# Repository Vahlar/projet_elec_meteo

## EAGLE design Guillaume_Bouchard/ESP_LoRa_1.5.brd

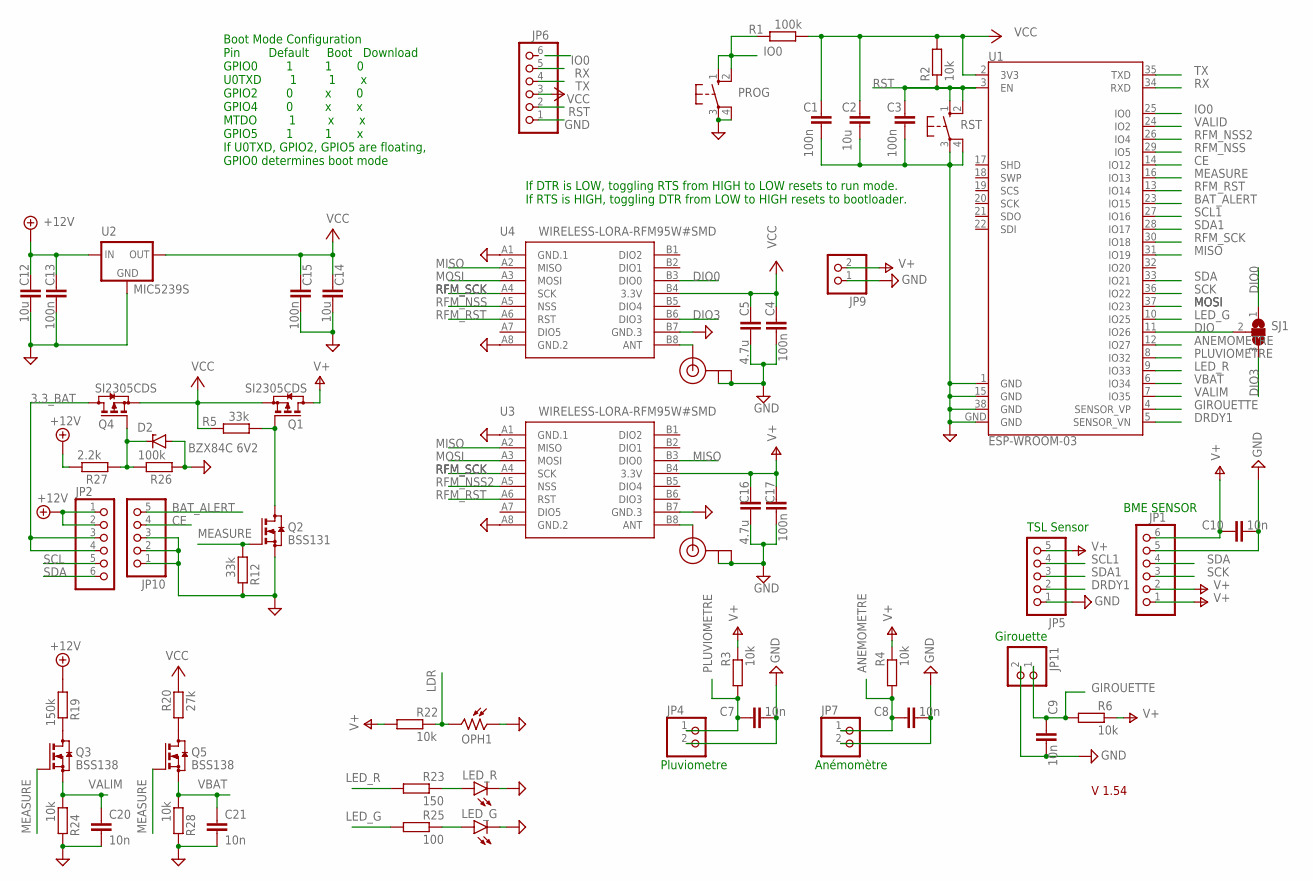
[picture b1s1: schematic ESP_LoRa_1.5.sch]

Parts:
C1, C3, C4, C13, C15, C17: 100n; C1206
C2, C12, C14: 10u; C1210
C5, C16: 4.7u; C1210
C7, C8, C9, C10, C20, C21: 10n; C1206
D2: BZX84C 6V2; TO236
J1, J2: U.FL
JP1, JP2, JP6: PINHD-1X6; 1X06
JP4, JP7, JP9, JP11: PINHD-1X2; 1X02
JP5, JP10: PINHD-1X5; 1X05
LED_G: LEDSMT1206; 1206
LED_R: LEDSMT1206; 1206
OPH1: VT93N2; VT900
PROG: 10-XX; B3F-10XX
Q1, Q4: SI2305CDS; SOT23
Q2: BSS131; SOT23
Q3, Q5: BSS138; SOT23
R1, R26: 100k; R1206
R2, R3, R4, R6, R22, R24, R28: 10k; R1206
R5, R12: 33k; R1206
R19: 150k; R1206
R20: 27k; R1206
R23: 150; R1206
R25: 100; R1206
R27: 2.2k; R1206
RST: 10-XX; B3F-10XX
SJ1: SJ2W; SJ_2
U1: ESP-WROOM-03
U2: MIC5239S; SOT223
U3, U4: WIRELESS-LORA-RFM95W#SMD

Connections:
3.3_BAT: JP2.3, JP2.4, Q4.3 (D)
+12V: C12.1, C13.1, JP2.1, JP2.2, R19.1, R27.2, U2.1 (IN)
ANEMOMETRE: C8.1, JP7.1, R4.1, U1.12 (IO27)
ANT2: J2.3 (SIGNAL), U4.B8 (ANT)
ANT3: J1.3 (SIGNAL), U3.B8 (ANT)
BAT_ALERT: JP10.5, U1.23 (IO15)
CE: JP10.4, U1.14 (IO12)
DIO: SJ1.2, U1.11 (IO26)
DIO0: SJ1.1, U4.B3 (DIO0)
DIO3: SJ1.3, U4.B6 (DIO3)
DRDY1: JP5.2, U1.5 (SENSOR_VN)
GIROUETTE: C9.1, JP11.1, R6.1, U1.4 (SENSOR_VP)
GND: C1.2, C2.2, C3.2, C4.2, C5.2, C7.2, C8.2, C9.2, C10.2, C12.2, C13.2, C14.2, C15.2, C16.2, C17.2, C20.2, C21.2, D2.A, J1.1 (GND), J1.2 (GND), J2.1 (GND), J2.2 (GND), JP1.5, JP4.2, JP5.1, JP6.1, JP7.2, JP9.1, JP10.1, JP10.2, JP10.3, JP11.2, LED_G.C, LED_R.C, OPH1.1, PROG.3, PROG.4 (P1), Q2.2 (S), R12.2, R24.2, R26.1, R28.2, RST.3, RST.4 (P1), U1.1 (GND), U1.15 (GND), U1.38 (GND), U1.GND, U2.2 (GND), U2.4 (GND), U3.A1 (GND.1), U3.A8 (GND.2), U3.B7 (GND.3), U4.A1 (GND.1), U4.A8 (GND.2), U4.B7 (GND.3)
IO0: PROG.1 (S), PROG.2 (S1), R1.2, U1.25 (IO0)
LDR: OPH1.2, R22.2
LED_G: R25.1, U1.10 (IO25)
LED_R: R23.1, U1.9 (IO33)
MEASURE: Q2.1 (G), Q3.1 (G), Q5.1 (G), R12.1, U1.16 (IO13)
MISO: U1.31 (IO19), U3.A2 (MISO), U3.B3 (DIO0), U4.A2 (MISO)
MOSI: U1.37 (IO23), U3.A3 (MOSI), U4.A3 (MOSI)
unnamed: Q1.1 (G), Q2.3 (D), R5.1
unnamed: Q3.3 (D), R19.2
unnamed: Q5.3 (D), R20.1
unnamed: LED_R.A, R23.2
unnamed: LED_G.A, R25.2
unnamed: D2.C, Q4.1 (G), R26.2, R27.1
PLUVIOMETRE: C7.1, JP4.1, R3.1, U1.8 (IO32)
RFM_NSS: U1.29 (IO5), U4.A5 (NSS)
RFM_NSS2: U1.26 (IO4), U3.A5 (NSS)
RFM_RST: U1.13 (IO14), U3.A6 (RST), U4.A6 (RST)
RFM_SCK: U1.30 (IO18), U3.A4 (SCK), U4.A4 (SCK)
RST: C3.1, JP6.2, R2.1, RST.1 (S), RST.2 (S1), U1.3 (EN)
RX: JP6.5, U1.34 (RXD)
SCK: JP1.3, U1.36 (IO22)
SCL: JP2.5
SCL1: JP5.4, U1.27 (IO16)
SDA: JP1.4, JP2.6, U1.33 (IO21)
SDA1: JP5.3, U1.28 (IO17)
TX: JP6.4, U1.35 (TXD)
V+: C10.1, C16.1, C17.1, JP1.1, JP1.2, JP1.6, JP5.5, JP9.2, Q1.3 (D), R3.2, R4.2, R6.2, R22.1, U3.B4 (3.3V)
VALID: U1.24 (IO2)
VALIM: C20.1, Q3.2 (S), R24.1, U1.7 (IO35)
VBAT: C21.1, Q5.2 (S), R28.1, U1.6 (IO34)
VCC: C1.1, C2.1, C4.1, C5.1, C14.1, C15.1, JP6.3, Q1.2 (S), Q4.2 (S), R1.1, R2.2, R5.2, R20.2, U1.2 (3V3), U2.3 (OUT), U4.B4 (3.3V)

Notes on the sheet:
If DTR is LOW, toggling RTS from HIGH to LOW resets to run mode. If RTS is HIGH, toggling DTR from LOW to HIGH resets to bootloader.
Boot Mode Configuration Pin Default Boot Download GPIO0 1 1 0 U0TXD 1 1 x GPIO2 0 x 0 GPIO4 0 x x MTDO 1 x x GPIO5 1 1 x If U0TXD, GPIO2, GPIO5 are floating, GPIO0 determines boot mode
V 1.54
TSL Sensor
BME SENSOR
Pluviometre
Anémomètre
Girouette

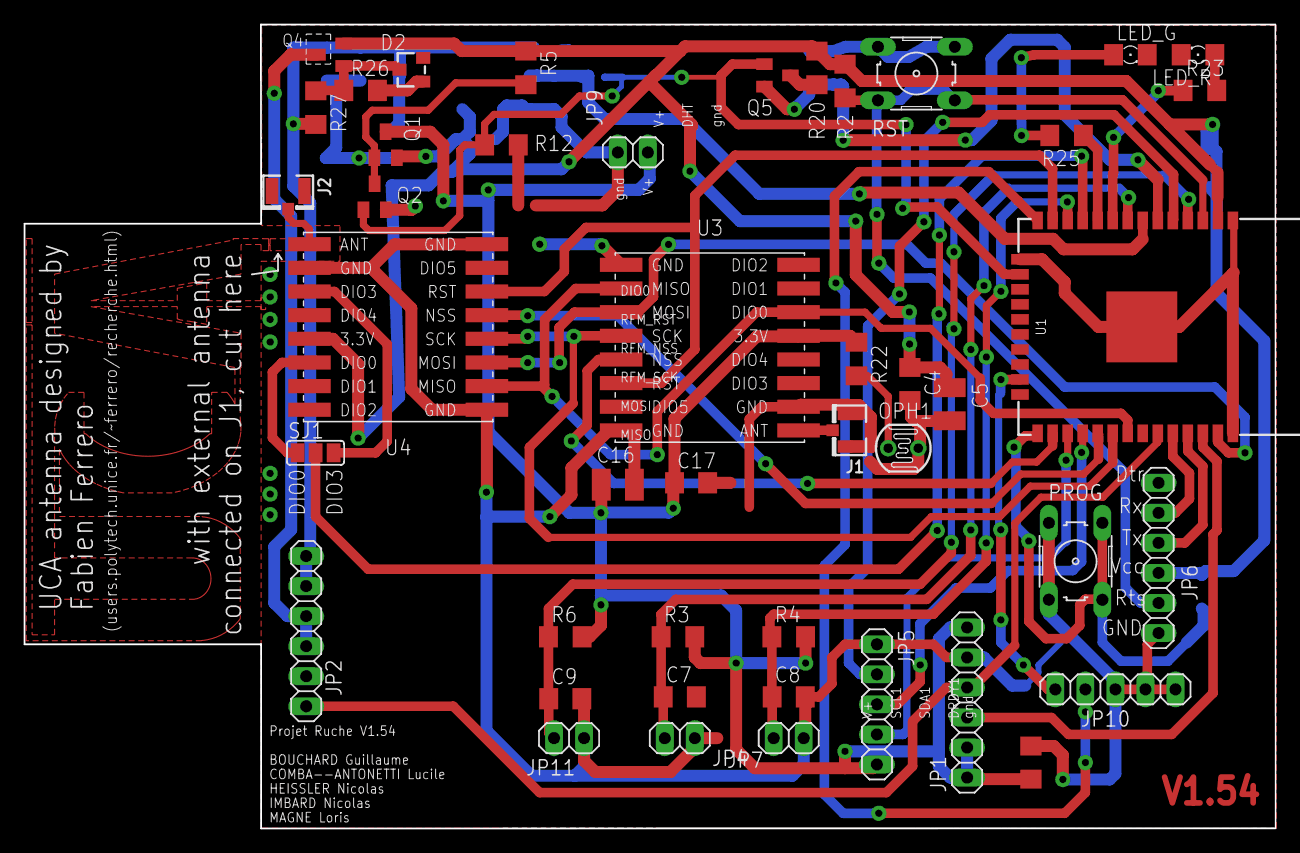
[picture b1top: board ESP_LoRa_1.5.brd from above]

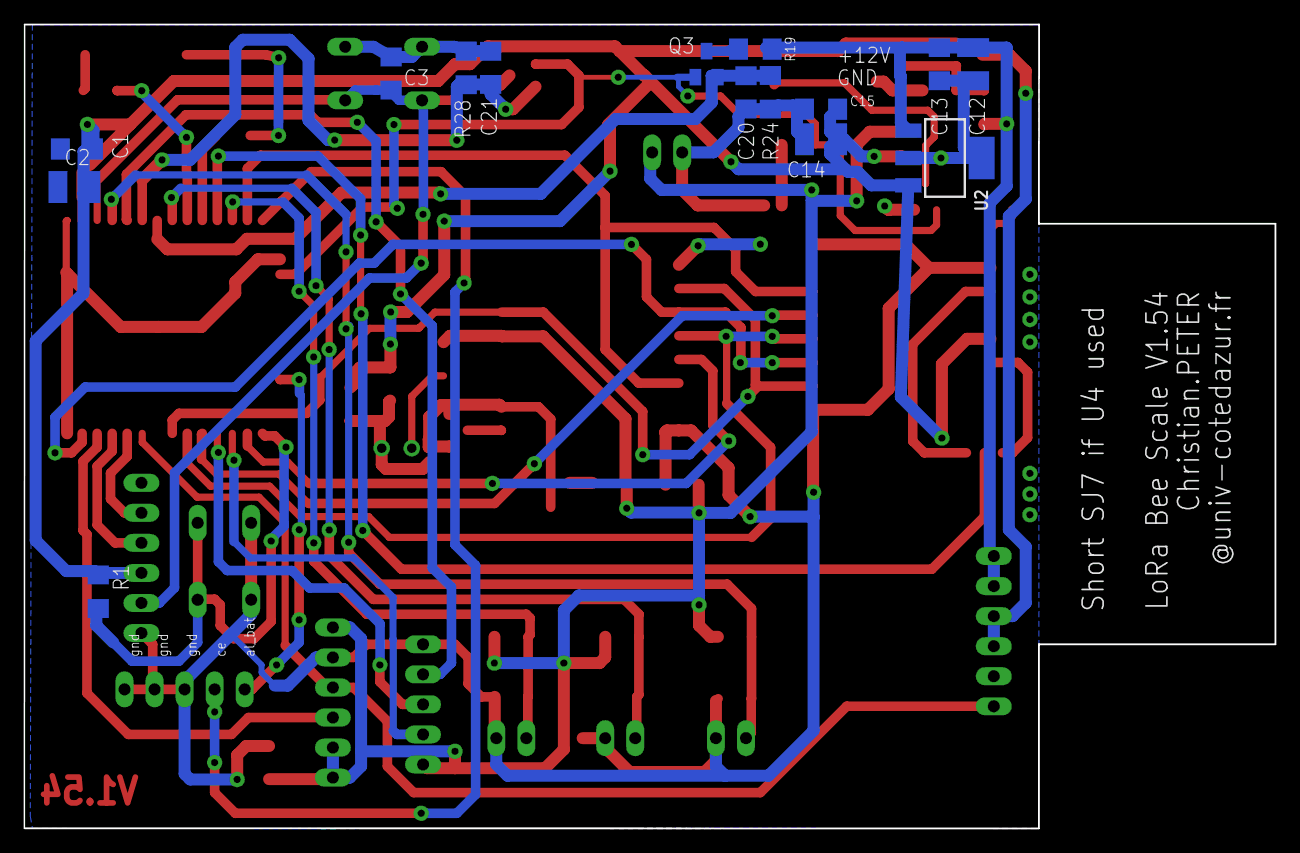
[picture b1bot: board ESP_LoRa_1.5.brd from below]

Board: 2 copper layers, 105.8 x 68.0 mm, 60 parts (15 on the bottom side), 42 nets.

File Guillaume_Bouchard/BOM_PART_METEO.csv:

"Qty";"Value";"Device";"Package";"Parts";"Description";"MF";"MPN";"OC_FARNELL";"OC_NEWARK";"POPULARITY";"SPICEMODEL";"SPICEPREFIX";
"2";"";"10-XX";"B3F-10XX";"PROG, RST";"OMRON SWITCH";"";"B3F-1000";"176432";"36M3542";"72";"";"";
"2";"";"LEDSMT1206";"1206";"LED_G, LED_R";"LED";"";"";"";"";"20";"";"";
"4";"";"PINHD-1X2";"1X02";"JP4, JP7, JP9, JP11";"PIN HEADER";"";"";"";"";"98";"";"";
"2";"";"PINHD-1X5";"1X05";"JP5, JP10";"PIN HEADER";"";"";"";"";"69";"";"";
"3";"";"PINHD-1X6";"1X06";"JP1, JP2, JP6";"PIN HEADER";"";"";"";"";"79";"";"";
"1";"";"SJ2W";"SJ_2";"SJ1";"SMD solder JUMPER";"";"";"";"";"7";"";"";
"1";"100";"RR1206";"R1206";"R25";"RESISTOR, European symbol";"";"";"";"";"";"NONE";"R";
"2";"100k";"RR1206";"R1206";"R1, R26";"RESISTOR, European symbol";"";"";"";"";"";"NONE";"R";
"6";"100n";"CC1206";"C1206";"C1, C3, C4, C13, C15, C17";"CAPACITOR, European symbol";"";"";"";"";"";"NONE";"C";
"7";"10k";"RR1206";"R1206";"R2, R3, R4, R6, R22, R24, R28";"RESISTOR, European symbol";"";"";"";"";"";"NONE";"R";
"6";"10n";"CC1206";"C1206";"C7, C8, C9, C10, C20, C21";"CAPACITOR, European symbol";"";"";"";"";"";"NONE";"C";
"3";"10u";"CC1210";"C1210";"C2, C12, C14";"CAPACITOR, European symbol";"";"";"";"";"";"NONE";"C";
"1";"150";"RR1206";"R1206";"R23";"RESISTOR, European symbol";"";"";"";"";"";"NONE";"R";
"1";"150k";"RR1206";"R1206";"R19";"RESISTOR, European symbol";"";"";"";"";"";"NONE";"R";
"1";"2.2k";"RR1206";"R1206";"R27";"RESISTOR, European symbol";"";"";"";"";"";"NONE";"R";
"1";"27k";"RR1206";"R1206";"R20";"RESISTOR, European symbol";"";"";"";"";"";"NONE";"R";
"2";"33k";"RR1206";"R1206";"R5, R12";"RESISTOR, European symbol";"";"";"";"";"";"NONE";"R";
"2";"4.7u";"CC1210";"C1210";"C5, C16";"CAPACITOR, European symbol";"";"";"";"";"";"NONE";"C";
"1";"BSS131";"BSS131";"SOT23";"Q2";"N-CHANNEL MOS FET";"";"";"";"";"";"";"";
"2";"BSS138";"BSS138";"SOT23";"Q3, Q5";"N-CHANNEL MOS FET";"";"";"";"";"";"";"";
"1";"BZX84C 6V2";"BZX84CSMD";"TO236";"D2";"Z DIODE";"";"";"";"";"1";"";"";
"1";"ESP-WROOM-03";"ESP-WROOM-03";"ESP-WROOM-03";"U1";"";"";"";"unknown";"";"";"";"";
"1";"MIC5239S";"MIC5239S";"SOT223";"U2";"LDO REGULATOR";"";"";"";"";"";"";"";
"2";"SI2305CDS";"SI2305CDS";"SOT23";"Q1, Q4";"P-CHANNEL MOS FET";"";"";"";"";"";"";"";
"2";"U.FL";"U.FL";"U.FL";"J1, J2";"U.FL Antenna Connector";"";"";"";"";"";"";"";
"1";"VT93N2";"VT93N2";"VT900";"OPH1";"Photoconductive Cell VT900 Series";"";"";"";"";"0";"";"";
"2";"WIRELESS-LORA-RFM95W#SMD";"WIRELESS-LORA-RFM95W#SMD";"WIRELESS-LORA-RFM95W#SMD";"U3, U4";"868/915 MHz LoRa Radio Transceiver Module based on SX1276 chip";"";"";"";"";"";"";"";

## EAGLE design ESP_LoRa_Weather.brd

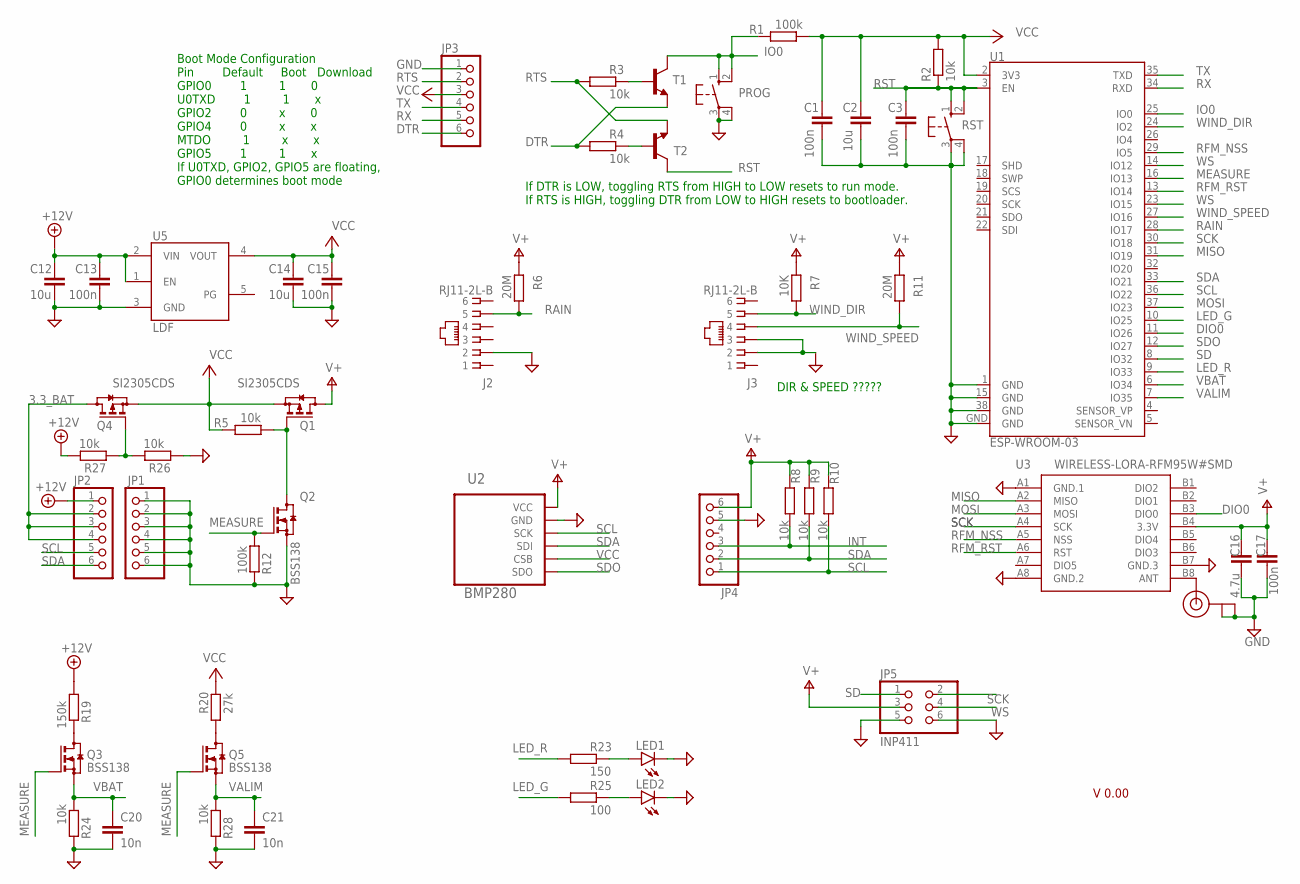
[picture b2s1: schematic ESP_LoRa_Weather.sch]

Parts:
C1, C3, C13, C15, C17: 100n; C1206
C2, C12, C14: 10u; C1210
C16: 4.7u; C1210
C20, C21: 10n; C1206
J1: U.FL
J2, J3: RJ11-2L-B; RJ11-NO_SHIELD
JP1, JP2, JP3, JP4: PINHD-1X6; 1X06
JP5: INP411; 2X03
LED1, LED2: LEDCHIPLED_0805; CHIPLED_0805
PROG: 10-XX; B3F-10XX
Q1, Q4: SI2305CDS; SOT23
Q2, Q3, Q5: BSS138; SOT23
R1, R12: 100k; R1206
R2, R3, R4, R5, R8, R9, R10, R24, R26, R27, R28: 10k; R1206
R6, R11: 20M; R1206
R7: 10K; R1206
R19: 150k; R1206
R20: 27k; R1206
R23: 150; R1206
R25: 100; R1206
RST: 10-XX; B3F-10XX
T1, T2: MMBT2222ALT1-NPN-SOT23-BEC; SOT23-BEC
U1: ESP-WROOM-03
U2: BMP280
U3: WIRELESS-LORA-RFM95W#SMD
U5: LDF3.3; PPAK

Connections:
3.3_BAT: JP2.2, JP2.3, JP2.4, Q4.3 (D)
+12V: C12.1, C13.1, JP2.1, R19.1, R27.2, U5.1 (EN), U5.2 (VIN)
DIO0: U1.11 (IO26), U3.B3 (DIO0)
DTR: JP3.6, R4.1, T1.E
GND: C1.2, C2.2, C3.2, C12.2, C13.2, C14.2, C15.2, C16.2, C17.2, C20.2, C21.2, J1.1 (GND), J1.2 (GND), J2.2, J3.2, J3.3, JP1.1, JP1.2, JP1.3, JP1.4, JP1.5, JP1.6, JP3.1, JP4.5, JP5.5, JP5.6, LED1.C, LED2.C, PROG.3, PROG.4 (P1), Q2.2 (S), R12.2, R24.2, R26.1, R28.2, RST.3, RST.4 (P1), U1.1 (GND), U1.15 (GND), U1.38 (GND), U1.GND, U2.GND, U3.A1 (GND.1), U3.A8 (GND.2), U3.B7 (GND.3), U5.3 (GND)
INT: JP4.3, R8.2
IO0: PROG.1 (S), PROG.2 (S1), R1.2, T1.C, U1.25 (IO0)
LED_G: R25.1, U1.10 (IO25)
LED_R: R23.1, U1.9 (IO33)
MEASURE: Q2.1 (G), Q3.1 (G), Q5.1 (G), R12.1, U1.16 (IO13)
MISO: U1.31 (IO19), U3.A2 (MISO)
MOSI: U1.37 (IO23), U3.A3 (MOSI)
unnamed: Q1.1 (G), Q2.3 (D), R5.1
unnamed: Q3.3 (D), R19.2
unnamed: J1.3 (SIGNAL), U3.B8 (ANT)
unnamed: Q5.3 (D), R20.1
unnamed: LED1.A, R23.2
unnamed: LED2.A, R25.2
unnamed: R3.2, T1.B
unnamed: R4.2, T2.B
unnamed: Q4.1 (G), R26.2, R27.1
RAIN: J2.5, R6.2, U1.28 (IO17)
RFM_NSS: U1.29 (IO5), U3.A5 (NSS)
RFM_RST: U1.13 (IO14), U3.A6 (RST)
RST: C3.1, R2.1, RST.1 (S), RST.2 (S1), T2.C, U1.3 (EN)
RTS: JP3.2, R3.1, T2.E
RX: JP3.5, U1.34 (RXD)
SCK: JP5.2, U1.30 (IO18), U3.A4 (SCK)
SCL: JP2.5, JP4.1, R10.2, U1.36 (IO22), U2.SCK
SD: JP5.1, U1.8 (IO32)
SDA: JP2.6, JP4.2, R9.2, U1.33 (IO21), U2.SDI
SDO: U1.12 (IO27), U2.SD0 (SDO)
TX: JP3.4, U1.35 (TXD)
V+: C16.1, C17.1, JP4.6, JP5.3, Q1.3 (D), R6.1, R7.1, R8.1, R9.1, R10.1, R11.1, U2.VCC, U3.B4 (3.3V)
VALIM: C21.1, Q5.2 (S), R28.1, U1.7 (IO35)
VBAT: C20.1, Q3.2 (S), R24.1, U1.6 (IO34)
VCC: C1.1, C2.1, C14.1, C15.1, JP3.3, Q1.2 (S), Q4.2 (S), R1.1, R2.2, R5.2, R20.2, U1.2 (3V3), U2.CSB, U5.4 (VOUT)
WIND_DIR: J3.5, R7.2, U1.24 (IO2)
WIND_SPEED: J3.4, R11.2, U1.27 (IO16)
WS: JP5.4, U1.14 (IO12), U1.23 (IO15)

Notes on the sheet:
If DTR is LOW, toggling RTS from HIGH to LOW resets to run mode. If RTS is HIGH, toggling DTR from LOW to HIGH resets to bootloader.
Boot Mode Configuration Pin Default Boot Download GPIO0 1 1 0 U0TXD 1 1 x GPIO2 0 x 0 GPIO4 0 x x MTDO 1 x x GPIO5 1 1 x If U0TXD, GPIO2, GPIO5 are floating, GPIO0 determines boot mode
V 0.00
DIR & SPEED ?????

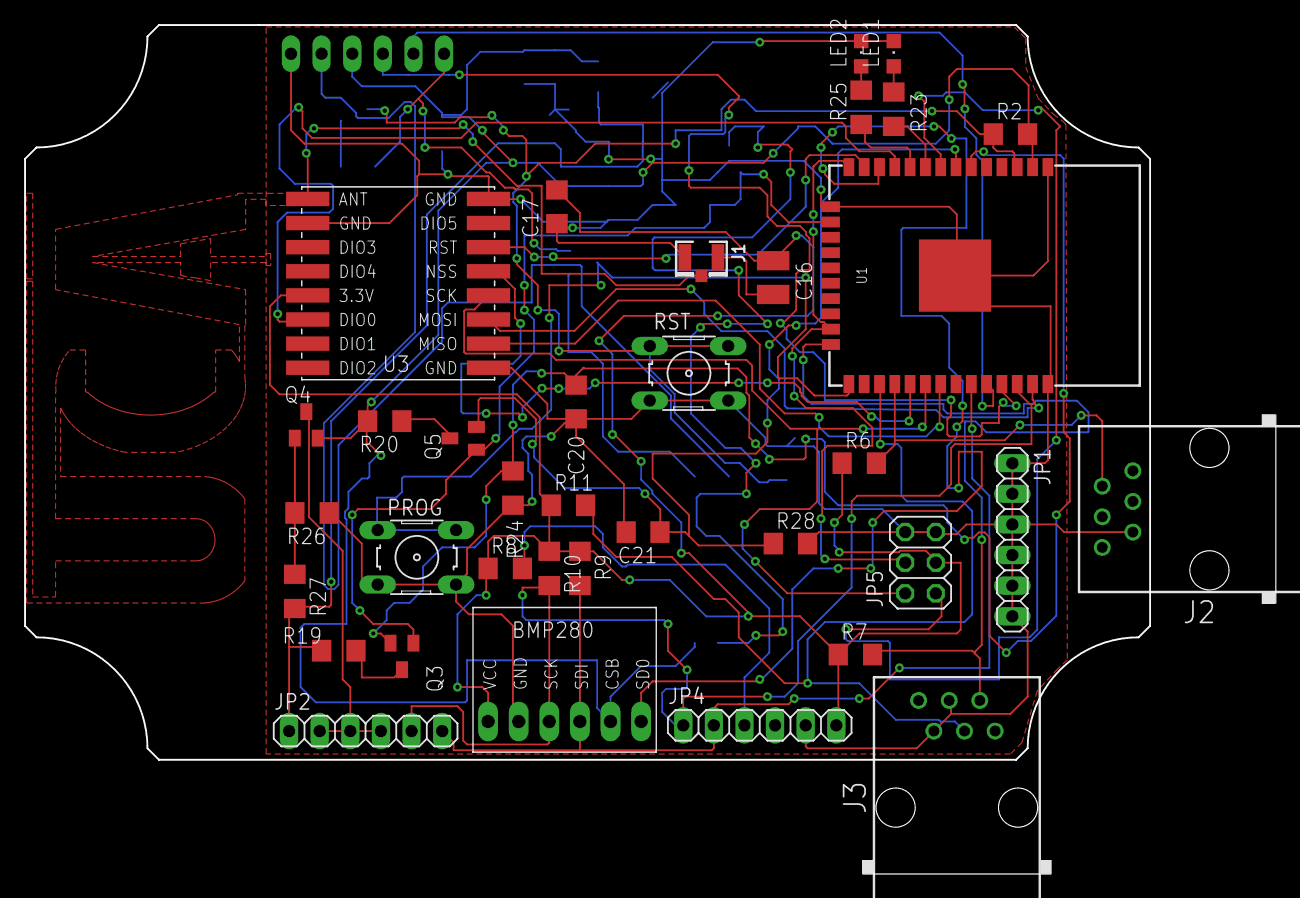
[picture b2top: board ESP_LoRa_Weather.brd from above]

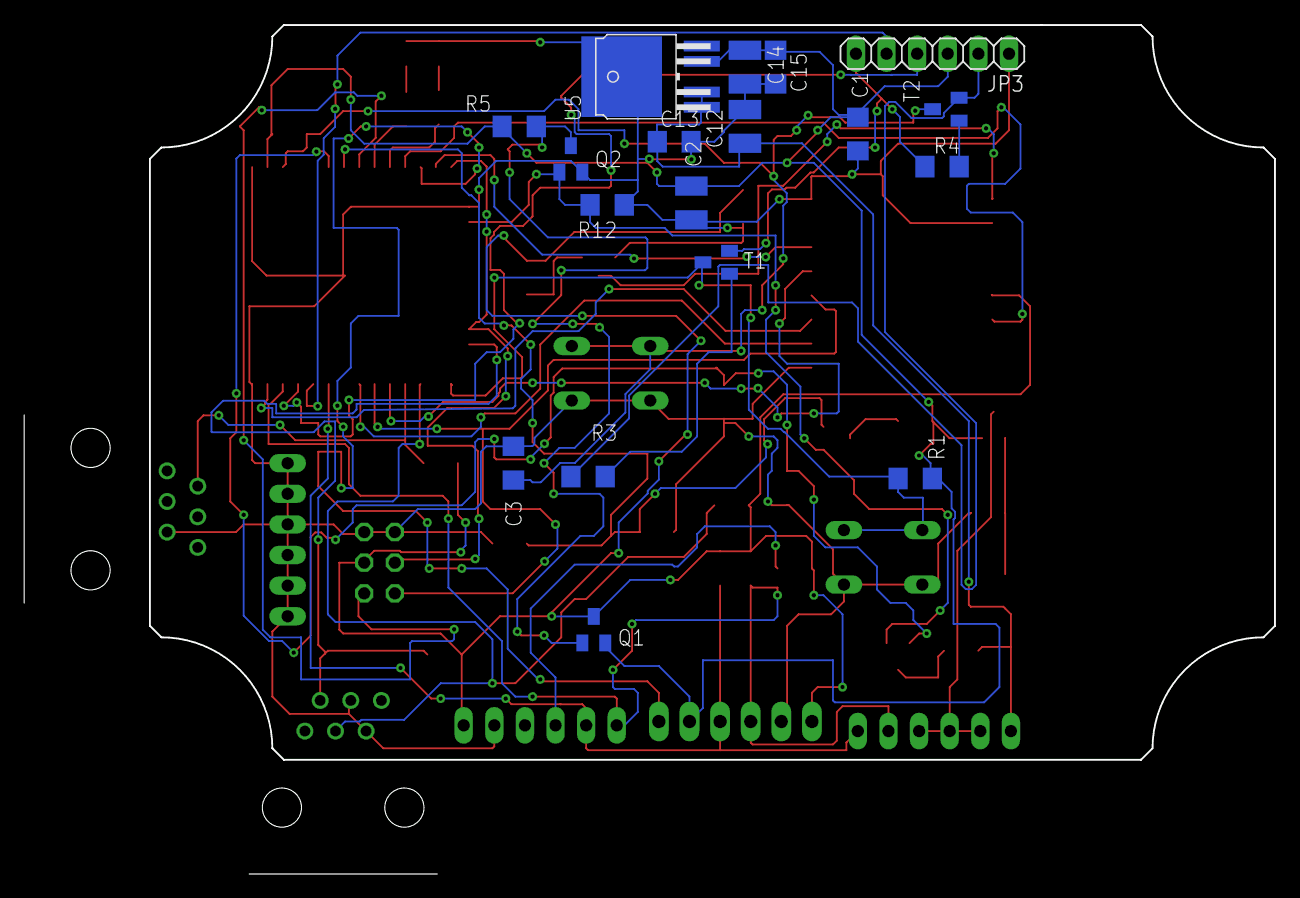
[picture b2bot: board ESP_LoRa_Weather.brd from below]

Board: 2 copper layers, 103.7 x 70.4 mm, 54 parts (18 on the bottom side), 40 nets.

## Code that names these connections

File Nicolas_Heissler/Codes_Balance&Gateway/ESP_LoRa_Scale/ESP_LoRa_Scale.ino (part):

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char    buf_mass[10];

// GPIO
#define MEASURE 13
#define LED_R 33
#define LED_G 25
#define LDR_PIN ADC1_CHANNEL_0 // 36 (PCB V1.10  27)
#define VBAT_PIN  ADC1_CHANNEL_6 //34
#define K_VBAT 0.272 // Vadc/Vbat = 0.265 ; R2/(R1+R2)= 0.27027027 R1=27k R2=10k
// K_VBAT = 0.27 => Vbat = Vextern from 3.3 to 3V ; Vbat = 2.7V @ Vextern = 2.75V ; Vbat = 2.4V @ Vextern = 2.47V
#define VALIM_PIN ADC1_CHANNEL_7 //35
#define K_VALIM 0.052 // Vadc/Valim = 0.06025@12V 0.06012@5V ; R2/(R1+R2)= 0.0625 R1=150k R2=10k
#define VALID_BTN 2   // K_VALIM = 0.052 => Valim = 5V @ Vextern = 5V   ; Valim = 3.65V @ Vextern = 4V 
#define NEXT_BTN  4   //                    Valim = 14V @ Vextern = 12V ; Valim = 12.7V @ Vextern = 11V ; Valim = 11.4V @ Vextern = 10V
#define PROG_BTN 0    // K_VALIM = 0.059 => Valim = 12V @ Vextern = 12V ; Valim = 11.2V @ Vextern = 11V ; Valim = 10.15V@ Vextern = 10V
// LoRa pins
#define SS 5   // 5  - 18 TTGO
#define RST 14
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// I2C pins : NAU7802 N°2
#define SDA1  17
#define SCL1  16
#define DRDY1 39  // not used !

#include <Wire.h>
#include <SPI.h>
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  timerAlarmEnable(wdt_timer); //enable interrupt
  timerWrite(wdt_timer, 0); //reset timer (feed watchdog)

  pinMode(MEASURE, OUTPUT);
  digitalWrite(MEASURE, LOW); // Peripherals power off
  pinMode(LED_R, OUTPUT);
  pinMode(LED_G, OUTPUT);
  //pinMode(LDR_PIN,INPUT);

  /* We set our ESP32 to wake up for an external trigger.
    There are two types for ESP32, ext0 and ext1 .
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  // measure power and LDR voltages
  adc_power_on();
  adc1_config_width(ADC_WIDTH_BIT_12);
  valim = get_voltage((adc1_channel_t)VALIM_PIN, ADC_ATTEN_0db , 20, (float)K_VALIM);
  DEBUGPRINT3("Valim  = "); DEBUGPRINT3(valim); DEBUGPRINTLN3(" V");
  vbat  = get_voltage((adc1_channel_t)VBAT_PIN , ADC_ATTEN_0db , 20, (float)K_VBAT );
  DEBUGPRINT3("Vbat  = "); DEBUGPRINT3(vbat); DEBUGPRINTLN3(" V");
  vldr  = get_voltage((adc1_channel_t)LDR_PIN  , ADC_ATTEN_11db , 20, (float)1 );
  DEBUGPRINT3("Vldr  = "); DEBUGPRINT3(vldr); DEBUGPRINTLN3(" V");
  if ( vldr < (vbat * 0.9) ) { //( vldr < vbat / 2 ) {
    //day = true;
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  }

  // blinking green led during measures
  tickerSetLow.attach_ms(BLINK_TIME_ON, setPinLow, LED_G);
  tickerSetHigh.attach_ms(BLINK_TIME_OFF, setPinHigh, LED_G);

  // ----------------- scale ------------
  // first get/set nb of sensors
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
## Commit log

2020-09-10 init
2020-09-10 add docs
2020-09-10 Create Nicolas_Imbard
2020-09-10 Create Loris_Magne
2020-09-10 Create txt
2020-09-10 Create test
2020-09-10 test push
2020-09-10 Test utilisation push
2020-09-10 Suppression du fichier inutile + copie du code arduino
2020-09-10 Suppression de test + Mise a jour du document taches projet
2020-09-10 Comment effectuer un push
2020-09-10 Modif fichier Taches
2020-09-10 Supression fichier .docx
2020-09-10 Push rapport séance 10-09
2020-09-10 Mise à jour du fichier des tâches par séance
2020-09-10 MAJ tâches par séances
2020-09-10 MAJ doc.md
2020-09-10 MAJ tâche par séance
2020-09-25 -Mise à jour du code 1.0 -> 1.1 -Création d'un fichier test pour le capteur BME -Création d'un fichier texte avec des infos sur le projet pour mon utilisation
2020-09-25 -Modification du fichier de test du capteur BME -Création du fichier de test du capteur TSL
2020-10-08 -Test files for BME and TSL validated -New test files to test both captor at the same time
2020-10-08 Rename seance-10-09.md to CR séance.md
2020-10-08 -Mise à jour du fichier de suivi de séance -Création d'un fichier de test pour le module LoRa
2020-10-22 Schéma de câblage carte RF96 LoRa
2020-10-22 -Création/Modification des fichiers de tests pour les modules LoRa -Mise à jour du fichier de suivi d'activités de séance
2020-11-19 Changement fichiers md
2020-11-19 Ajout des codes donnés par le prof (gateway et balance)
2020-11-19 Déscription fonctionnement Gateway
2020-11-26 -Modification des fichiers de test anémomètre et pluviomètre
2020-11-26 -Changement du code de test d'envoi de commande LoRa -Modification du fichier de suivi de séance -Mise à jour du programme arduino complet (en cours de construction)
2020-12-03 - Modification du code de test de l'anemomètre - Ajout d'une photo prise sur un oscillo (interruption anemometre) - Ajout de la documentation des capteurs météo
2020-12-04 -Modification fonctionnelle du code de l'anémometre -Modification fonctionnelle du code du pluviometre -Changement de l'image de l'oscillo
2020-12-04 -Modification du test de l'anémometre -Modification du test du pluviometre -Nouveau fichier de test pluviometre+deepSleep
2020-12-10 Modification du code de la girouette
2020-12-11 -Travail du 11/12/2020
2020-12-17 schematic
2020-12-17 -Modification du code de deepSleep -MAJ du doc des activités de séances
2020-12-17 Update To_Know
2021-01-08 -Powerpoint + ordinogramme + code deepsleep
2021-01-15 Ajout présentation mi-parcours
2021-01-29 -Changement du fichier de suivi pour mise en page du fichier md
2021-01-29 -Développement du code deepSleep avec des méthodes à jour -Ancien code de test du deepsleep passé en DEPRECATED -Développement des codes d'envoi/réception pour le module LoRa -Mise à jour du fichier 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
2021-01-29 -Update du fichier de suivi
2021-02-12 -Modification du code de reception sur module LoRa pour s'adapter au câblage et à la fréquence utilisée pour l'envoi
2021-02-12 -Changement du code receiver
2021-02-19 -Création d'un code de test pour envoi/reception via 2 module LoRa sur un seul ESP32 -Mise à jour du fichier de suivi pour la séance dela semaine dernière -Passage de la version 1.1 en 1.0 BETA 1 (lo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
2021-03-05 -Maj du fichier de suivi pour le 19/02/2021
2021-03-19 Tableaux de correspondances tension en fonction de la direction du vent Girouette Travail sur la présentation finale
2021-03-19 Mise à jour tableau des correspondance Girouette
2021-04-01 maj PCB
2021-04-01 MAJ code Girouette
2021-04-01 Shéma élec fonctionnement Girouette Mise à jour graphique tableau de correspondance Girouette
2021-04-02 Modification des code de tests de reception LoRa pour reception avec interruption Remplissage du fichier de suivi de travail de séance
2021-04-15 -Code principal modifié -Fichier de suivi rempli

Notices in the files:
Nicolas_Heissler/Codes_Balance&Gateway/ESP_LoRa_Scale/ESP_LoRa_Scale.ino:
All rights reserved.
This program and the accompanying materials are made available under the terms of the MIT License
parts and their libraries:
diy-modules: Released under the Creative Commons Attribution 4.0 International License: http://creativecommons.org/licenses/by/4.0
micrel: Copyright (C) 2008, Bob Starr
